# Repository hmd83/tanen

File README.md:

<h1>
  <picture>
    <source media="(prefers-color-scheme: dark)" srcset="site/tanenbase-lockup-dark.svg">
    
  </picture>
</h1>

**Open-source LoRaWAN hive scale** · *Offene Stockwaage* · [العربية](README.ar.md) · [tanen.eu](https://tanen.eu)

A LoRaWAN beehive monitor that runs for years on three AAA primary lithium cells.

It weighs the hive, reads its temperature — and, with optional Bluetooth sensors,
temperature and humidity inside the hive — and reports over LoRaWAN to The Things
Network — then sleeps at about **4 µA**. Configuration and calibration happen
over Bluetooth from a web page, so there is no mobile app to install and nothing
to plug in once the lid is closed.

| | |
|---|---|
| **MCU** | Seeed Studio XIAO nRF54LM20A (Standard, non-Sense) |
| **Radio** | Wio-SX1262 LoRa kit — LoRaWAN Class A, OTAA, EU868 |
| **Sensors** | NAU7802 24-bit load-cell ADC · DS18B20 temperature · nPM1300 battery gauge · optional: up to 3 SwitchBot Outdoor Meter BLE temperature/humidity sensors (Extended Mode) |
| **RTOS / SDK** | Zephyr 4.4 via nRF Connect SDK v3.4.0 |
| **Sleep current** | ~4 µA (System OFF + GRTC wake) |
| **Battery life** | ~4.6 years on 3× AAA Li/FeS₂ (1200 mAh) at 15 min / 2 h reporting — ~10 y at 60 min / 4 h. With Extended Mode BLE sensors each uplink costs 139 mC instead of 63 mC: ~3.3 y / ~7 y |
| **Uplink** | 8 bytes — weight (999 kg range), temperature, battery, flags · +5 bytes per BLE sensor heard (max 23) |

*A node in the field: the hive stands on the platform, the IP-rated enclosure
bolted to it holds the electronics and the battery pack, and the temperature probe
runs inside the hive.*

📺 **[Build workshop walkthrough (YouTube)](https://www.youtube.com/watch?v=t2ags30G7-o)** ·
🎬 **[Bench test clip](media/test.mp4)** (download — GitHub does not play repo-hosted video inline)

---

## In the field: apiary in Bühl (Baden)

A TanenBase runs under a hive in Bühl, Baden. It reports over LoRaWAN to a
gateway on Windeck Castle, about 4 km away, and sends one reading an hour.

| | |
|---|---|
| **Radio link** | ≈ 4 km to the gateway (3.6 km line of sight) |
| **Reporting** | once an hour |
| **Gateway** | Kerlink iStation, Windeck Castle, 378 m above sea level |
| **Live data** | 📈 **[beelogger dashboard — Bühl apiary](https://community.beelogger.de/tanen/beelogger1/beelogger_show.php)** (weight and temperature, updated hourly) |

*Left to right: the hive on its platform, the enclosure with the red setup button
underneath; the gateway tower on Windeck Castle; the 3.6 km path from the
gateway to the apiary.*

---

## How it works

The firmware is a **single-pass state machine**, not a loop. Every wake is a cold
boot from System OFF: it checks why it woke, does one pass, and powers off again.

```
       wake reason
            │
    ┌───────▼────────┐  button / reset
    │     SETUP      │  BLE config service, sensors live, 180 s window
    └───────┬────────┘
            │
    ┌───────▼────────┐  timer
    │  MEASUREMENT   │  weight + temp + battery, anomaly check
    └───────┬────────┘
            │ delta exceeded, or heartbeat due?
    ┌───────▼────────┐  yes
    │  TRANSMISSION  │  BLE sensor scan (Extended Mode), SX1262 up, join if needed, uplink
    └───────┬────────┘
            │
    ┌───────▼────────┐
    │     SLEEP      │  System OFF, GRTC timed wake
    └────────────────┘
```

The radio is only powered when there is something to send. Between heartbeats
the node measures, compares against the last transmitted values, and goes back
to sleep without ever touching the SX1262 — which is where most of the battery
life comes from.

Full design notes: [`docs/ARCHITECTURE.md`](docs/ARCHITECTURE.md).

### Temperature compensation

A hive scale's real enemy is not resolution, it is thermal drift. Uncompensated,
the reference cell reports a **350 g peak-to-peak swing on a constant 22 kg
load** over a 17.5 K daily cycle — 16 g of phantom weight per kelvin, enough to
bury a real nectar flow.

The firmware corrects it with two parameters: one gain constant, plus a
first-order lag filter on the probe temperature that models the probe sitting a
few minutes behind the aluminium cell body. Residual scatter drops **6.5×, to
σ = 15.7 g**. The filtered temperature is carried in ZMS across System OFF, and
the tare stores the temperature it ran at as the correction's reference point.

*Same 22 kg load, 40.7 h, one daily temperature cycle. σ 102.2 g → 15.7 g,
peak-to-peak 350 g → 103 g.*

**Validated in the field**, not just on the bench: six days outdoors with a
22.2 kg dead weight and the correction live left **+1.10 g/K** of temperature
sensitivity where the uncompensated cell had −16.6, and σ of 11.6 g against
63.1 g — measured on the *same samples*, by reconstructing the filter offline
and inverting the correction.

*Days 4–6 are rain, not drift: +220 g arrived in two hours while the filtered
temperature moved 0.4 K, and 506 g of water was still in the wooden platform and
the concrete block at the end. Once the drying trend is modelled, the residual
thermal term across those days is +0.56 and −1.48 g/K — the correction holds
underneath the water.*

*The cell the shipped coefficient was fitted on — a Bosche H40A-C3-0150 single-point
cell bolted between two steel spreader plates. Worth staring at: the report
concludes the drift is **not** coming from the cell but from this mount, which
is 8× outside the OIML R60 envelope the cell is certified to.*

`k` is a property of the **cell plus its mount**, not of the cell alone —
re-characterise after any mechanical change. Which cell is fitted is therefore a
**runtime setting**, not a build flag: the setup page offers a generic cell (no
correction), the measured H40A-C3-0150 and Steinberg SBS-PF-150, three
named-but-uncharacterised cells (Zemic L6E, TAL220, Flintec PC/SB — they run
uncorrected but the unit records which is fitted), or your own measured gain
and lag, and the correction picks its constants up from there.
Profile table and how to characterise a cell:
[`docs/load_cells/`](docs/load_cells/). Method, data, hold-out validation and
the (unflattering) hardware conclusions for the reference cell:
[`docs/load_cells/H40A-C3-0150/`](docs/load_cells/H40A-C3-0150/); the
SBS-PF-150, fitted from a production week instead of a bench run:
[`docs/load_cells/SBS-PF-150/`](docs/load_cells/SBS-PF-150/).

### Extended Mode — a look inside the hive

The scale tells you *that* a colony gained or lost weight. It cannot tell you
whether the colony is raising brood, holding its winter cluster, or sitting in
damp air. **Extended Mode** adds up to three off-the-shelf **SwitchBot Outdoor
Meter** Bluetooth sensors — at most two inside the hive and one outside — and
sends their temperature and humidity in the same uplink as the weight. No cable
through the hive wall and no extra gateway: the node's own nRF54LM20A radio
listens for them.

<p align="center">
  
  &nbsp;&nbsp;
  
</p>

*Left: a sensor with its Tanen label — the Bluetooth address as text and as a QR
code. Right: sensors live on the setup page, two in the hive and one outside.*

- **Set up from the phone.** In the web page's *Erweitert* tab, scan the label's
  QR code (or type the address), choose *inside the hive* or *outside*, save.
  Readings appear within seconds, on that tab and on the overview.
- **Straight into BEEP and beelogger.** The outside sensor becomes `t` / `TempOut`
  (the DS18B20 moves to BEEP's `t_0`); the in-hive sensors map to `t_i`/`h_i`,
  `TempIn`/`FeuchteIn` and `TempIn2`/`FeuchteIn2`. Nothing to change on either
  platform.
- **Only when it counts.** The node scans for the sensors only on wakes that
  transmit and stops as soon as every sensor has been heard. Each sensor adds
  5 bytes to the uplink; one that is not heard costs no airtime and sets a flag
  instead.
- **What it costs.** A transmit wake with the scan measures **139 mC** instead of
  63 mC, so the pack lasts about **3.3 years** instead of 4.6 at 15 min / 2 h
  ([`docs/POWER_BUDGET.md`](docs/POWER_BUDGET.md)).

Wire format and GATT details:
[`docs/ARCHITECTURE.md`](docs/ARCHITECTURE.md#extended-mode-blocks).

---

## Repository layout

| Path | What it is |
|------|------------|
| [`src/`](src/) | Firmware — `core/` (FSM, power, watchdog), `drivers/`, `features/`, `config/` |
| [`boards/`](boards/) | Application devicetree overlay for the target board |
| [`third_party/`](third_party/) | Vendored Seeed XIAO nRF54LM20A board definition (Apache-2.0) |
| [`Tanen_Base_pcb/`](Tanen_Base_pcb/) | KiCad carrier board — schematic, layout, gerbers |
| [`web/`](web/) | Web Bluetooth configuration page + standalone downlink encoder (no build step) |
| [`ttndecoder/`](ttndecoder/) | TTN payload formatters — one unified BEEP + beelogger decoder, plus the older per-platform ones |
| [`test_apps/measure_loop/`](test_apps/measure_loop/) | Standalone sensor bring-up app |
| [`docs/`](docs/) | Architecture, power budget, sprint log, TRD, open questions, German user manual (`BENUTZERHANDBUCH.md` + built HTML) |
| [`docs/load_cells/`](docs/load_cells/) | Load-cell characterisation — data, analysis, host replay of the compensation |
| [`media/`](media/) | Build photos and a bench-test clip |

---

## Building

**Requires** nRF Connect SDK **v3.4.0** and its bundled toolchain. The board
definition is out-of-tree and vendored, so no `west update` of extra manifests is
needed.

```powershell
git clone https://github.com/hmd83/tanen.git
cd tanen

# LoRaWAN credentials — never commit the real one
Copy-Item prj_credentials.conf.example prj_credentials.conf
#   then edit it and set your AppKey

.\build.ps1 debug        # logs on uart20 -> on-board CMSIS-DAP VCOM @115200
.\build.ps1 prod         # LOG off, size-optimized
.\flash_update.ps1       # flash, preserving stored config + calibration
```

`build.ps1` finds the SDK automatically (newest `vX.Y.Z` under `C:\ncs`). Override
with `$env:NCS_ROOT`, `$env:NCS_VERSION`, or `$env:NCS_TOOLCHAIN` if your install
lives elsewhere. On a mode change it forces `--pristine` for you, because
switching in place trips a stale-CMakeCache Kconfig failure.

Raw `west` equivalent, if you prefer:

```sh
west build -b xiao_nrf54lm20a/nrf54lm20a/cpuapp --no-sysbuild -- \
    -DBOARD_ROOT=$PWD/third_party/seeed-xiao-nrf54lm20a \
    -DOVERLAY_CONFIG="prj_credentials.conf;prj_production.conf"
```

**Gotchas worth knowing before your first build** — see
[`docs/PLAN.md`](docs/PLAN.md) Sprint 15 for the full list:

- Keep the build directory path **short** on Windows (MAX_PATH kills ninja).
- Do **not** add `-S cdc-acm-console`. It repoints the console at the nRF's own
  USBHS CDC, which never enumerates on this board — you get silence.
- pyocd cannot program the nRF54LM20A: its erase works, then its flash algorithm
  hard-faults and leaves the chip blank. Use OpenOCD (what `flash_*.ps1` do) or
  `west flash`.

---

## Provisioning a node

1. Flash, then press the user button to enter **SETUP**. The node advertises as
   `TanenBase` for 180 seconds.
2. Open [`web/index.html`](web/index.html) in Chrome or Edge (Web Bluetooth;
   Safari and Firefox do not support it) and connect.
3. Write the DevEUI, JoinEUI, and AppKey from your TTN device registration.
4. Tare the empty scale, then calibrate with a known reference weight. The tare
   also records the temperature it ran at — that becomes the reference point of
   the thermal correction, so tare at a temperature the hive actually sees.
5. Set the measurement and transmit intervals, and the anomaly thresholds.
6. Press **Done**. The node joins TTN and enters its normal cycle.

Everything above is also settable later by LoRaWAN downlink (FPort 10–13) and
persists in ZMS across reboots and firmware updates.
[`web/encoder.html`](web/encoder.html) builds those downlinks — pick the
parameter, type the value in human units, and copy the fPort plus hex/base64 for
the TTN console, or the whole `down/push` body for the TTN API. It is a separate
page with no Bluetooth at all, so it needs neither the node nor a pairing.

**Each physical unit needs its own DevEUI.** Leave `CONFIG_TANENBASE_DEV_EUI`
empty to derive a unique one from the SoC's factory hardware ID.

### The Things Network

Register the device as **LoRaWAN MAC v1.0.3**, OTAA, EU868, then install
[`ttndecoder/tanen-decoder.js`](ttndecoder/tanen-decoder.js) as the uplink
payload formatter (Payload formatters → Uplink → Custom Javascript formatter).

One formatter serves both supported platforms: it parses the frame once (8 bytes,
plus 5 per Bluetooth sensor in Extended Mode) and emits both key sets into the
same `decoded_payload`.

| Reading | BEEP key | beelogger key | Unit |
|---|---|---|---|
| Weight | `weight_kg` | `Gewicht` | kg |
| Temperature | `t` | `TempOut` | °C |
| Battery | `bv` | `VBatt` | V |
| Outside temp / humidity (BLE) | `t` / `h` | `TempOut` / `FeuchteOut` | °C / %RH |
| Inside #1 temp / humidity (BLE) | `t_i` / `h_i` | `TempIn` / `FeuchteIn` | °C / %RH |
| Inside #2 temp / humidity (BLE) | `t_1` / — | `TempIn2` / `FeuchteIn2` | °C / %RH |

**Extended Mode** adds up to three SwitchBot Outdoor Meters (at most two inside
the hive, one outside), set up in the web page's *Erweitert* tab by typing the
sensor's MAC or scanning a QR label. The node scans for them only on wakes that
transmit. An outside sensor takes over `t` / `TempOut` and the DS18B20 moves to
BEEP's `t_0`; without one, `t` / `TempOut` stay the DS18B20. Wire format in
[`docs/ARCHITECTURE.md`](docs/ARCHITECTURE.md#extended-mode-blocks).

Each platform stores the keys it knows and ignores the rest, so no per-platform
formatter juggling is needed. A failed sensor decodes to `null` on both sides,
never to a sentinel number. `flags`, `anomaly_weight`, `anomaly_temp` and
`heartbeat` ride along for TTN live-data debugging and are ignored by both
servers. The older single-platform formatters
([`beepdecoder.js`](ttndecoder/beepdecoder.js),
[`tanen-beelogger-decoder.js`](ttndecoder/tanen-beelogger-decoder.js)) are kept
for reference.

**BEEP** ([beep.nl](https://beep.nl)) — the webhook base URL **must** carry the
device key explicitly:

```
https://api.beep.nl/api/lora_sensors?key=<DevEUI>
```

Without it BEEP decodes your payload perfectly and then silently drops it,
because it falls back to a TTN Stack **V2** field (`payload_fields.hardware_serial`)
that V3 webhooks do not send. This one cost real debugging time — see
[`docs/PLAN.md`](docs/PLAN.md) Sprint 14.

**beelogger** ([beelogger.de](https://beelogger.de)) — the community server
takes the `Gewicht` / `TempOut` / `VBatt` names its own payload formatter uses,
which is exactly what the decoder emits. Webhook base URL:

```
https://community.beelogger.de/<username>/{/devID}/beelogger_log.php?Passwort=<password>&LORA=1
```

- `<username>` — your community-server account
- `{/devID}` — filled in by TTN per uplink, so name the TTN devices
  `beelogger1`, `beelogger2`, … to match the stations registered on the server
- `<password>` — the same one for every station, which is what lets a **single
  webhook serve the whole TTN application** instead of one per node
- `LORA=1` — tells the server the record arrives via LoRaWAN

Both platforms are confirmed receiving from the unified decoder.

---

## Hardware

The carrier board is a passive breakout: XIAO socket, Wio-SX1262 socket, screw
terminals for the load cell and the DS18B20, battery input, and the bulk
capacitor. KiCad sources and fabricated gerbers are in
[`Tanen_Base_pcb/`](Tanen_Base_pcb/).

*Assembled in an IP-rated enclosure — XIAO nRF54LM20A top-left, NAU7802
load-cell amplifier on the right, external 868 MHz antenna, and cable glands for
the load cell and temperature probe.*

*The weighing platform end-on: a single-point cell carries the whole top frame
from the centre, so the hive can sit anywhere on it without changing the
reading. Enclosure sits on the top deck, cable runs down to the cell.*

*Underside — the cell between the top plate and the base, load arrow pointing
down. E<sub>max</sub> = 150 kg, which is oversized for a hive: a 100 kg cell
would give ~1.5× better signal-to-noise at the same absolute drift.*

**Optional Extended Mode sensors:** up to three SwitchBot Outdoor Meters (model
WoIOSensorTH), each on its own battery. Nothing to wire — print a label with the
sensor's Bluetooth address as plain text and as a QR code (for example
`EB:6B:01:C6:49:95`) and stick it on; the setup page reads either.

> The KiCad project files are still named **XIAO_nRF54L15 V1**, while the board
> itself is silkscreened *Tanen Base v0.1*. That is deliberate: all XIAO modules
> share one 21 × 17.5 mm footprint and pinout, so the nRF54L15 and nRF54LM20A are
> drop-in replacements on this carrier — only the GPIO number behind each header
> pin changes, and that is handled in the devicetree overlay.
> [`Tanen_Base_pcb/README.md`](Tanen_Base_pcb/README.md) has the full pin-by-pin
> mapping.

**Battery:** 3× BEVIGOR AAA 1.5 V lithium (Li/FeS₂, 1200 mAh) in series —
4.5 V nominal, **5.2 V measured fresh at room temperature** — **primary /
non-rechargeable**. The firmware
deliberately deletes `charging-enable` from the nPM1300 charger node; with it
armed, applying USB power would push charge current into non-rechargeable cells.
Do not re-enable it unless you have also changed the chemistry.

⚠️ **The pack sits above the nPM1300's recommended VBAT maximum for
essentially its whole life.** The window is 2.3–4.45 V recommended, 5.5 V
absolute. At µA drain Li/FeS₂ holds a ~1.79 V/cell plateau that is nearly
independent of depth of discharge and **rises with temperature**, so the pack
only drops back inside the recommended range as the cells die. Worst case is a
warm hive with cells at the top of the 1.79–1.83 V fresh spread: **5.49 V against
a 5.5 V absolute maximum.** This is a deliberate, documented deviation — see
[`docs/POWER_BUDGET.md`](docs/POWER_BUDGET.md) §5.2 for the chemistry data,
mitigations, the ER14505 AA Li-SOCl₂ cell this replaced, and what the swap bought
(no passivation, −40 °C rating, large pulse margin) and cost (9.3 y → 4.6 y).

Measure cells before assembly and reject any above ~1.80 V; keep the enclosure
out of direct sun.

---

## Status

Running in the field — see [the Bühl apiary](#in-the-field-apiary-in-bühl-baden). The core loop — measure, delta-detect, uplink, sleep — is
verified end to end on hardware, including ingestion by both BEEP and the
beelogger community server from the same uplink. Extended Mode is verified on
hardware too (2026-09-13): three sensors live in the setup page, their blocks in
the uplink, and the transmit wake measured on the PPK2.

Not yet done: MCUboot/OTA is wired up (`sysbuild.conf`, `pm_static.yml`) but
**unverified on this module**, and no production signing key is provisioned.
Open design questions are tracked in
[`docs/OPEN_QUESTIONS.md`](docs/OPEN_QUESTIONS.md).

---

## Contributing

See [CONTRIBUTING.md](CONTRIBUTING.md). Bug reports and hardware notes from
anyone running this on real hives are especially welcome.

---

## Credits

**Hussein Daj** — project owner, product design, hardware design (carrier PCB,
sensor selection, power architecture), firmware direction, and all hardware
bring-up, PPK2 power measurement, and field validation.

**[Claude Code](https://claude.com/claude-code)** (Anthropic) — firmware
co-development. Worked alongside the author on the state machine, drivers,
BLE GATT service, power-management path, watchdog and fault-tolerance layer, the
nRF54L15 → nRF54LM20A port, the load-cell temperature-drift analysis and the
compensation formula it produced, and this documentation. Every change was
reviewed and hardware-verified by the author before it landed.

**[Google Gemini](https://gemini.google.com)** — product design input:
requirements shaping, use-case analysis, and design-decision review during the
concept and specification phase.

### Third-party work this builds on

- [Zephyr RTOS](https://zephyrproject.org) and the
  [nRF Connect SDK](https://developer.nordicsemi.com) — Apache-2.0
- [Seeed Studio](https://github.com/Seeed-Studio/platform-seeedboards) — XIAO
  nRF54LM20A Zephyr board definition, vendored in
  [`third_party/`](third_party/) — Apache-2.0
- [loramac-node](https://github.com/Lora-net/LoRaMac-node) — LoRaWAN MAC
- [BEEP](https://beep.nl) — open beehive monitoring platform and data API
- [beelogger](https://beelogger.de) — open hive-scale project and community
  server; its field names are mirrored by the uplink decoder

---

## License

Apache-2.0 — see [LICENSE](LICENSE) and [NOTICE](NOTICE). This covers the
firmware, the hardware design files, and the documentation.

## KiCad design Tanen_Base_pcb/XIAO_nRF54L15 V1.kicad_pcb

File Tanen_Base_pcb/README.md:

# TanenBase carrier PCB

KiCad 7+ project for the TanenBase carrier board — the passive breakout that
holds the XIAO module, the Wio-SX1262 LoRa kit, the load-cell terminal block,
the DS18B20 terminal block, and the battery connections.

| File | Contents |
|------|----------|
| `XIAO_nRF54L15 V1.kicad_sch` | Schematic |
| `XIAO_nRF54L15 V1.kicad_pcb` | Board layout |
| `XIAO_nRF54L15_V1_Gerber/` | Gerbers + drill files (as fabricated) |
| `XIAO_nRF54L15_V1_Gerber.zip` | Same, zipped for the fab house |
| `simulation_image_top.png` / `_bottom.png` | 3D renders |

---

## Why is this named "nRF54L15" when the firmware targets the nRF54LM20A?

**Because the board does not care, and renaming it would invalidate a PCB that
has already been fabricated and verified.**

The Seeed Studio XIAO family is a fixed mechanical and electrical standard: all
XIAO modules share the same **21 × 17.5 mm** outline, the same two 7-pin 2.54 mm
headers, and the same pin *roles* in the same physical positions:

```
        ┌──────────────┐
   5V ──┤              ├── D0
  GND ──┤              ├── D1
  3V3 ──┤     XIAO     ├── D2
  D10 ──┤   21×17.5mm  ├── D3
   D9 ──┤              ├── D4
   D8 ──┤              ├── D5
   D7 ──┤              ├── D6
        └──────────────┘
```

The **XIAO nRF54L15** and the **XIAO nRF54LM20A** are drop-in mechanical
replacements for each other on this carrier. The footprint, the outline, the
castellated pads, the header pitch, and the power pin positions are identical.
Only the GPIO number sitting behind each header pin differs, and that is a
firmware concern, resolved entirely in the devicetree overlay
[`boards/xiao_nrf54lm20a_nrf54lm20a_cpuapp.overlay`](../boards/xiao_nrf54lm20a_nrf54lm20a_cpuapp.overlay).

So the KiCad project *filename* is historical — it records the module that was in
the socket when the board was laid out. The board itself is silkscreened
**"Tanen Base v0.1"**, not with any module name. The gerbers in this directory
are the ones that were actually fabricated; renaming the project would mean
regenerating them for zero electrical benefit.

### Header role mapping across both modules

Firmware keeps the header **roles** fixed, so the carrier's netlist is valid for
either module:

| XIAO Pin | Carrier net | nRF54L15 GPIO | nRF54LM20A GPIO |
|----------|-------------|---------------|-----------------|
| D0 | DS18B20 data (1-Wire) — mandatory K1 cut, see below | P1.04 | P1.00 |
| D1 | SX1262 DIO1 | P1.05 | P1.31 |
| D2 | SX1262 RST + external TanenButton | P1.06 | P1.30 |
| D3 | SX1262 BUSY | P1.07 | P1.29 |
| D4 | SX1262 NSS | P1.10 | P1.03 |
| D5 | LORA_RF_SW1 (Wio-SX1262 ant. switch) | P1.11 | P1.07 |
| D6 | NAU7802 SCL | P2.08 | P1.08 |
| D7 | NAU7802 SDA | P2.07 | P1.09 |
| D8 | SPI SCK | P2.01 | P1.04 |
| D9 | SPI MISO | P2.04 | P1.05 |
| D10 | SPI MOSI | P2.02 | P1.06 |

### Mandatory rework: cut the Wio-SX1262 K1 button off D0

The Wio-SX1262 for XIAO ships a user button **K1 (TS-1188E)** and a **10 kΩ
pull-up R2 to +3V3** on **D0** — the net this carrier uses for the DS18B20
1-Wire data line.

**This is not optional and not a corner case: with K1/R2 fitted, 1-Wire does not
read at all.** Observed on hardware. R2 lands in parallel with the carrier
1-Wire pull-up (~3.2 kΩ effective) on top of the switch stub loading; the exact
failure mechanism was not chased down because the cut fixes it outright.

**The cut:** the single trace from the K1/R2 node to the D0 castellated pad on
the Wio board. One cut lifts *both* K1 and R2 off D0 and leaves the D0
pass-through (XIAO → carrier → DS18B20 terminal) intact. Verify by continuity:
XIAO D0 still reaches the DS18B20 terminal, K1 node now isolated from D0.
**Done on the units built so far** — repeat it on every new Wio-SX1262 before
assembly, or temperature reads will fail on that unit.

**Optional afterwards:** the cut leaves K1 + R2 as a self-contained
button-with-pull-up, currently isolated and unused. Wiring that node to **P0.09**
on the XIAO — in parallel with the module own user button — makes K1 a second
TanenButton with **no firmware change**: P0.09 is already the armed System OFF
wake source (`gpio_disconnect_all()` in [`src/core/power.c`](../src/core/power.c))
and R2 reinforces the internal pull-up. P0.09 is not on any header, so that wire
has to land on the XIAO on-board switch pad.

### External button: D2 (P1.30) — shares the SX1262 NRESET net

> **Field-verified 2026-09-09** — bare switch to GND on D2, wake from System OFF
> into SETUP, no issues observed.

The second TanenButton lands on **D2 = P1.30**, the same net as the SX1262
**NRESET**. D2 is on a 7-pin header, so **carrier v0.1 already routes it** — no
flying wire, and v0.2 needs no new net. (It was on D19 = P0.00, a bottom pad,
until 2026-09-07; **D19 is now free**.)

Wiring: a plain momentary switch from D2 to GND. Nothing else — no pull-up, no
cap. The SoC's internal pull-up (R_PU = 12 / 14 / 16 kΩ min/typ/max) holds the
line high while the pin is sense-armed in System OFF, and that is also what
keeps the SX1262 out of reset.

**Why sharing a reset line is acceptable here.** SETUP is a once-a-year
calibration action and the station is asleep 99.8 % of the time (185 s awake per
day at T_meas = 900 s / T_tx = 14400 s, from `docs/POWER_BUDGET.md` §1):

- **Asleep (99.8 %)** — press pulls NRESET low: the SoC wakes *and* the SX1262
  resets. The radio reset is free, because every wake is a full SoC reset and
  the sx126x driver drives NRESET low at device init anyway.
- **Awake (0.2 %)** — the pin is a driver-owned output, so the press is not
  latched and is simply lost. Shorting a standard-drive pad to GND is harmless:
  I_OH,SD is 1 / 3 / 4 mA against a 15 mA recommended all-GPIO budget. The SETUP
  LED is the user's feedback — no LED, press again.
- **Switch fails closed** — NRESET held low: wake loop draining the cell *and* a
  radio stuck in reset. Missing uplinks make it visible server-side within one
  heartbeat interval.

Add **100 nF to GND** at the switch only if the button wire leaves the
enclosure. On D19 a coupled glitch cost a spurious boot; on D2 it also resets
the radio, possibly mid-TX. 100 nF against the ~14 kΩ pull-up is ~1.4 ms —
harmless next to the driver's 20 ms reset pulse.

Port note: any wake-capable port works. The nRF54LM20A datasheet *Port
capabilities* table lists P0, P1 and P3 as wakeup sources with pin sense/detect
and GPIOTE; **P2 has none of the three** and cannot wake the system at all.
Avoid D22/D23 (P0.03/P0.04 carry GRTC PWM / CLKOUT32K).

Firmware already supports it: `button_arm_sense()` in
[`src/core/power.c`](../src/core/power.c) arms P0.09 and P1.30 identically, and
either press wakes into SETUP.

### Differences that *are* worth knowing

These do not affect the carrier board, but they change firmware behaviour:

- **Battery sensing.** The nRF54L15 module has no PMIC — the L15 firmware read
  VBAT through a divider on an ADC pin. The **nRF54LM20A carries an on-board
  Nordic nPM1300**, and the firmware reads its factory-trimmed VBAT ADC instead.
  Nothing on the carrier changed; the divider was on the module side.
- **Antenna switch.** The L15 build had to sequence an RF switch on P2.03/P2.05.
  On the LM20A those pins belong to the on-board NOR flash. The Wio-SX1262 kit
  brings its own switch control out to header pin **D5 = P1.07 (LORA_RF_SW1)**;
  the firmware never drives it, because the radio is configured
  `dio2-tx-enable` and the SX1262 switches the path from DIO2. D5 is therefore
  **committed to an RF control net and is not a spare GPIO** — do not put a
  button, pull-up, or anything else on it.
- **On-board NOR flash.** The LM20A has a py25q64 on P2.00–P2.05. Firmware must
  put it into deep power-down before System OFF or it costs ~14 µA. Again,
  module-side only.

---

## Fabrication notes

- 2-layer board, standard 1.6 mm FR4, HASL or ENIG both fine.
- No components on the bottom layer other than the silkscreen.
- The 470 µF low-ESR bulk capacitor on the battery rail is **mandatory**, not
  optional — the LoRa TX burst peaks around 92 mA and the chosen ER14505 AA
  Li-SOCl₂ cell is rated 100 mA continuous. See
  [`docs/POWER_BUDGET.md`](../docs/POWER_BUDGET.md) §6.
- The battery input is wired straight to the XIAO **BAT** pin, i.e. the nPM1300
  VBAT input: **2.3 V min, 4.45 V max recommended, 5.5 V absolute**. Anything
  connected there must stay inside that window at fresh open-circuit *and* at
  end of life. See `docs/POWER_BUDGET.md` §8.

> **Safety:** the firmware deletes `charging-enable` from the nPM1300 charger
> node on purpose. This design runs a **primary, non-rechargeable** Li-SOCl₂
> cell. Do not fit a rechargeable cell and do not re-enable charging without
> changing both together.

---

## License

The hardware design files in this directory are released under the same
[Apache-2.0](../LICENSE) license as the rest of the project.

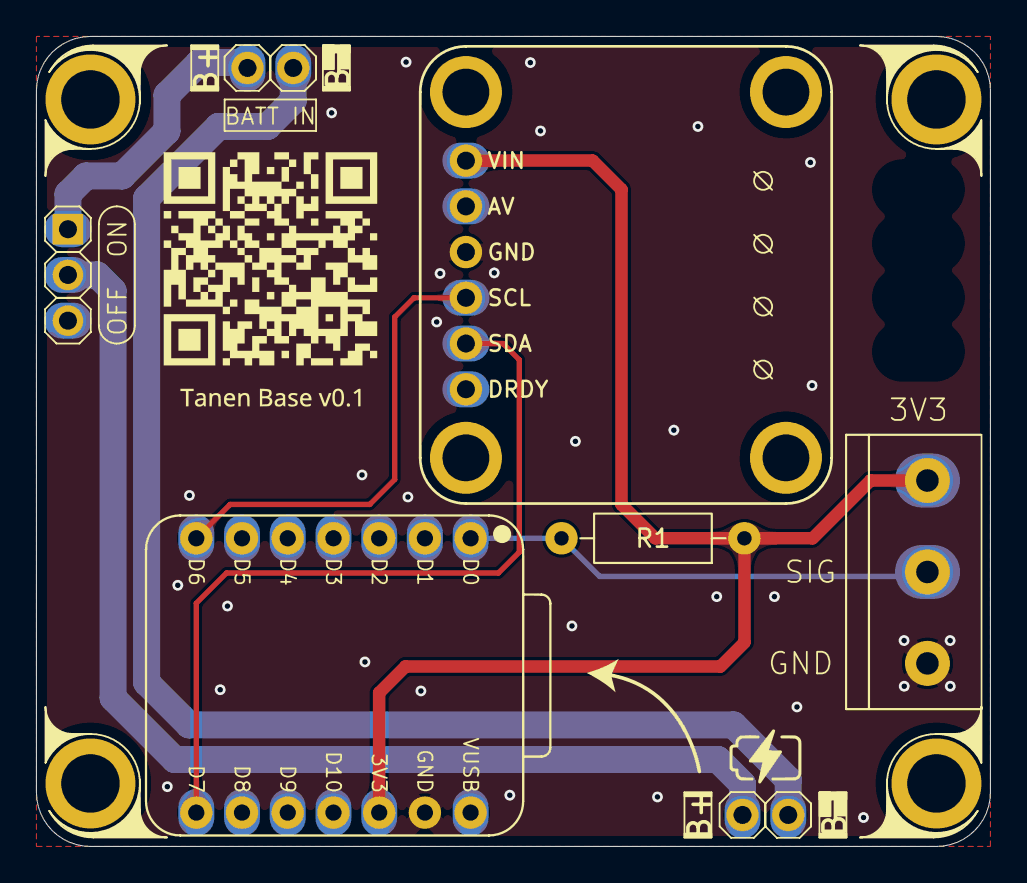
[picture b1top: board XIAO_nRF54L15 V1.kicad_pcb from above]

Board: 2 copper layers, 53.0 x 45.0 mm, 7 parts (0 on the bottom side), 8 nets.

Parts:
J1: Screw_Terminal_01x03; TerminalBlock-3_P5.08mm
J2: BATT IN; PinHeader_1x02_P2.54mm_Vertical
J3: SW; PinHeader_1x03_P2.54mm_Vertical
J4: BATT O; PinHeader_1x02_P2.54mm_Vertical
R1: 4K7; R_Axial_DIN0207_L6.3mm_D2.5mm_P10.16mm_Horizontal
U1: XIAO-nRF54l15
U2: NAU7802_Adafruit

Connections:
+3.3V: J1.1, R1.1, U1.12 (3V3), U2.1 (VIN)
/D0: J1.2, R1.2, U1.1 (D0)
/D6: U1.7 (D6), U2.4 (SCL)
/D7: U1.8 (D7), U2.5 (SDA)
GND: J1.3, U1.13 (GND), U2.3 (GND)
unnamed: J2.1, J3.1
unnamed: J2.2, J4.2
unnamed: J3.2, J4.1
